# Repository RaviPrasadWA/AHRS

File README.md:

# AHRS
An attitude and heading reference system (AHRS) for 450+ size HELI

# 3D Models on
https://grabcad.com/library/ahrs-case-2-1

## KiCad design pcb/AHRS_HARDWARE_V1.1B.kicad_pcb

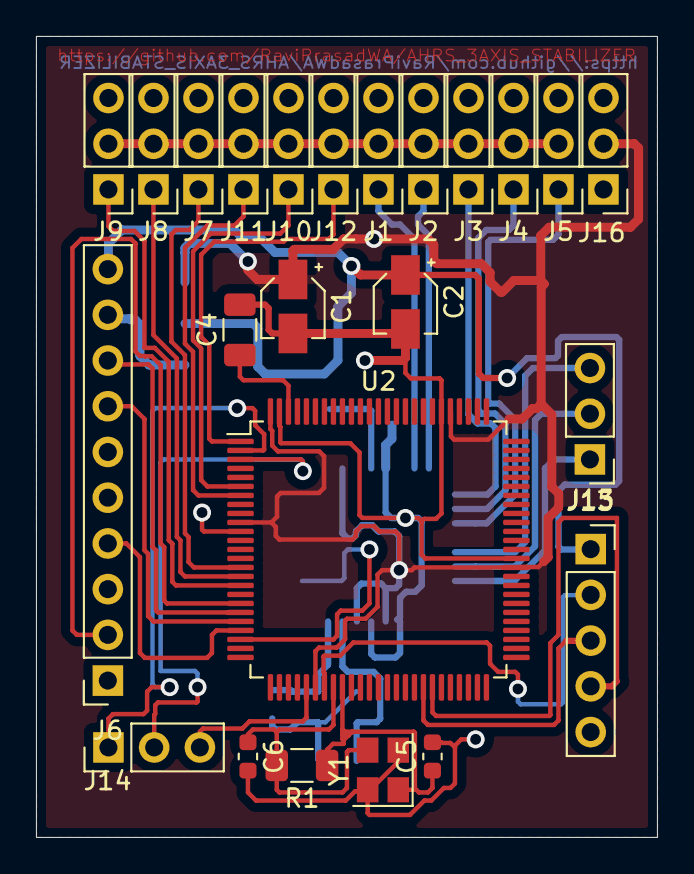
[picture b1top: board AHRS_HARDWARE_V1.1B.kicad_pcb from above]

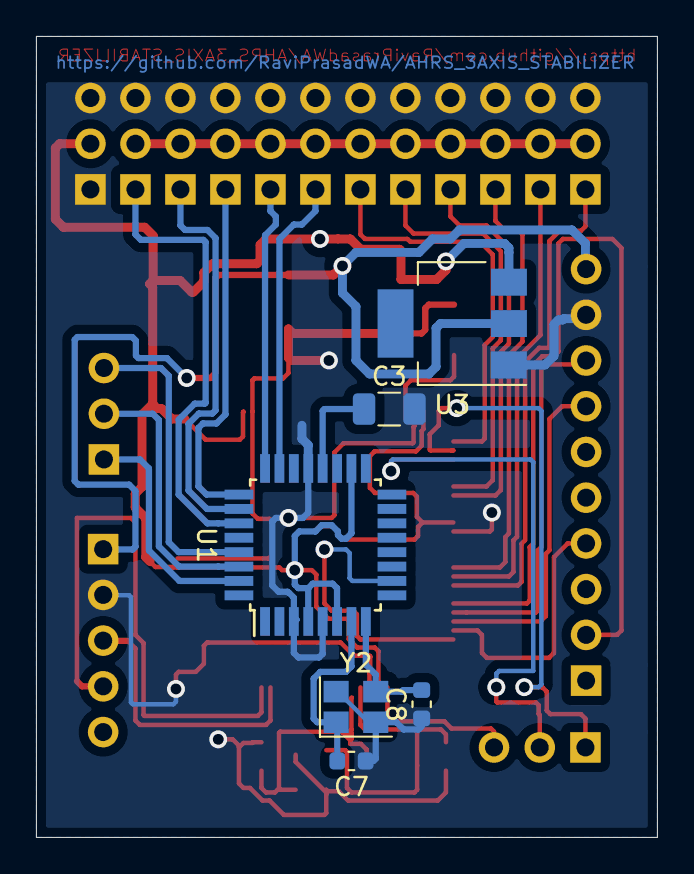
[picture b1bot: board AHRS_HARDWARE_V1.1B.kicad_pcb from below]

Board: 2 copper layers, 34.5 x 44.5 mm, 30 parts (6 on the bottom side), 34 nets.

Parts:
C1, C2: CP; CP_Elec_3x5.3
C3, C4: C; C_1206_3216Metric
C5, C6, C7, C8: 16pF; C_0603_1608Metric
J1: RC1; PinHeader_1x03_P2.54mm_Vertical
J2: RC2; PinHeader_1x03_P2.54mm_Vertical
J3: RC3; PinHeader_1x03_P2.54mm_Vertical
J4: RC4; PinHeader_1x03_P2.54mm_Vertical
J5: RC5; PinHeader_1x03_P2.54mm_Vertical
J6: MPU9250; PinSocket_1x10_P2.54mm_Vertical
J7: SV1; PinHeader_1x03_P2.54mm_Vertical
J8: SV2; PinHeader_1x03_P2.54mm_Vertical
J9: SV3; PinHeader_1x03_P2.54mm_Vertical
J10: SV4; PinHeader_1x03_P2.54mm_Vertical
J11: SV5; PinHeader_1x03_P2.54mm_Vertical
J12: SV6; PinHeader_1x03_P2.54mm_Vertical
J13: M8JTAG; PinHeader_1x03_P2.54mm_Vertical
J14: 2560MTAG; PinHeader_1x03_P2.54mm_Vertical
J15: HMC5883L; PinSocket_1x05_P2.54mm_Vertical
J16: Conn_01x03_Female; PinHeader_1x03_P2.54mm_Vertical
R1: 1M; R_1206_3216Metric
U1: ATmega328-AU; TQFP-32_7x7mm_P0.8mm
U2: ATmega2560-16AU; TQFP-100_14x14mm_P0.5mm
U3: LM1117-3.3; SOT-223
Y1, Y2: Crystal; Crystal_SMD_3225-4Pin_3.2x2.5mm

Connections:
+5V: J1.2, J2.2, J3.2, J4.2, J5.2, J7.2, J8.2, J9.2, J10.2, J11.2, J12.2
+5VA: C1.1, J16.2, U1.4, U1.6, U1.18, U2.10, U2.31, U2.61, U2.80, U2.100, U3.3
GND: C1.2, C2.2, C3.2, C4.2, C5.2, C6.2, C7.1, C8.1, J1.3, J2.3, J3.3, J4.3, J5.3, J6.9, J7.3, J8.3, J9.3, J10.3, J11.3, J12.3, J15.2, J16.1, J16.3, U1.3, U1.5, U1.21, U2.11, U2.32, U2.62, U2.81, U2.99, U3.1, Y1.2, Y1.4, Y2.2, Y2.4
unnamed: C2.1, J6.10, J15.1, U3.2
unnamed: C3.1, U1.20
unnamed: C4.1, U2.98
unnamed: C5.1, R1.1, U2.34, Y1.1
unnamed: C6.1, R1.2, U2.33, Y1.3
unnamed: C7.2, U1.7, Y2.1
unnamed: C8.2, U1.8, Y2.3
unnamed: J1.1, U1.23
unnamed: J2.1, U1.24
unnamed: J3.1, U1.25
unnamed: J4.1, U1.26
unnamed: J5.1, U1.27
unnamed: J6.2, U2.19
unnamed: J6.4, U2.22
unnamed: J6.7, U2.21
unnamed: J6.8, U2.20
unnamed: J7.1, U2.15
unnamed: J8.1, U2.16
unnamed: J9.1, U2.17
unnamed: J10.1, U2.6
unnamed: J11.1, U2.7
unnamed: J12.1, U2.1
unnamed: J13.1, U1.31
unnamed: J13.2, U1.30
unnamed: J13.3, U1.29
unnamed: J14.1, U2.2
unnamed: J14.2, U2.3
unnamed: J14.3, U2.30
unnamed: J15.3, U2.43
unnamed: J15.4, U2.44
unnamed: U1.10, U2.23

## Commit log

2020-11-01 removed the module from single repo and added them all here
2020-11-01 removed the older case pic updated with the new case pic
2020-11-08 added the modification + fillet to the case shape
2020-11-24 deleted the older files
2020-11-24 added the new case files
2020-11-24 modified the final assy
2020-11-24 added the modified step file
